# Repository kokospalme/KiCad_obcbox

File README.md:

# KiCad_obcbox
Hardware of the obcbox-project. This PCB is designed for a raspberry pi 3 B+ and an 0.96" OLED screen (be careful with the display-pinout!)
* Software (main): [java-BC](https://github.com/kokospalme/java-BC/tree/obcbox)
* Software (gui): [obcgui](https://github.com/kokospalme/obcgui/)
* Hardware (pcb): [KiCad_obcbox](https://github.com/kokospalme/KiCad_obcbox)
* Hardware (case): [grabcad](https://grabcad.com/library/obcbox-enclosure-v1-0-1)

# Status quo

* [v0.2 is working](https://github.com/kokospalme/KiCad_obcbox/releases)

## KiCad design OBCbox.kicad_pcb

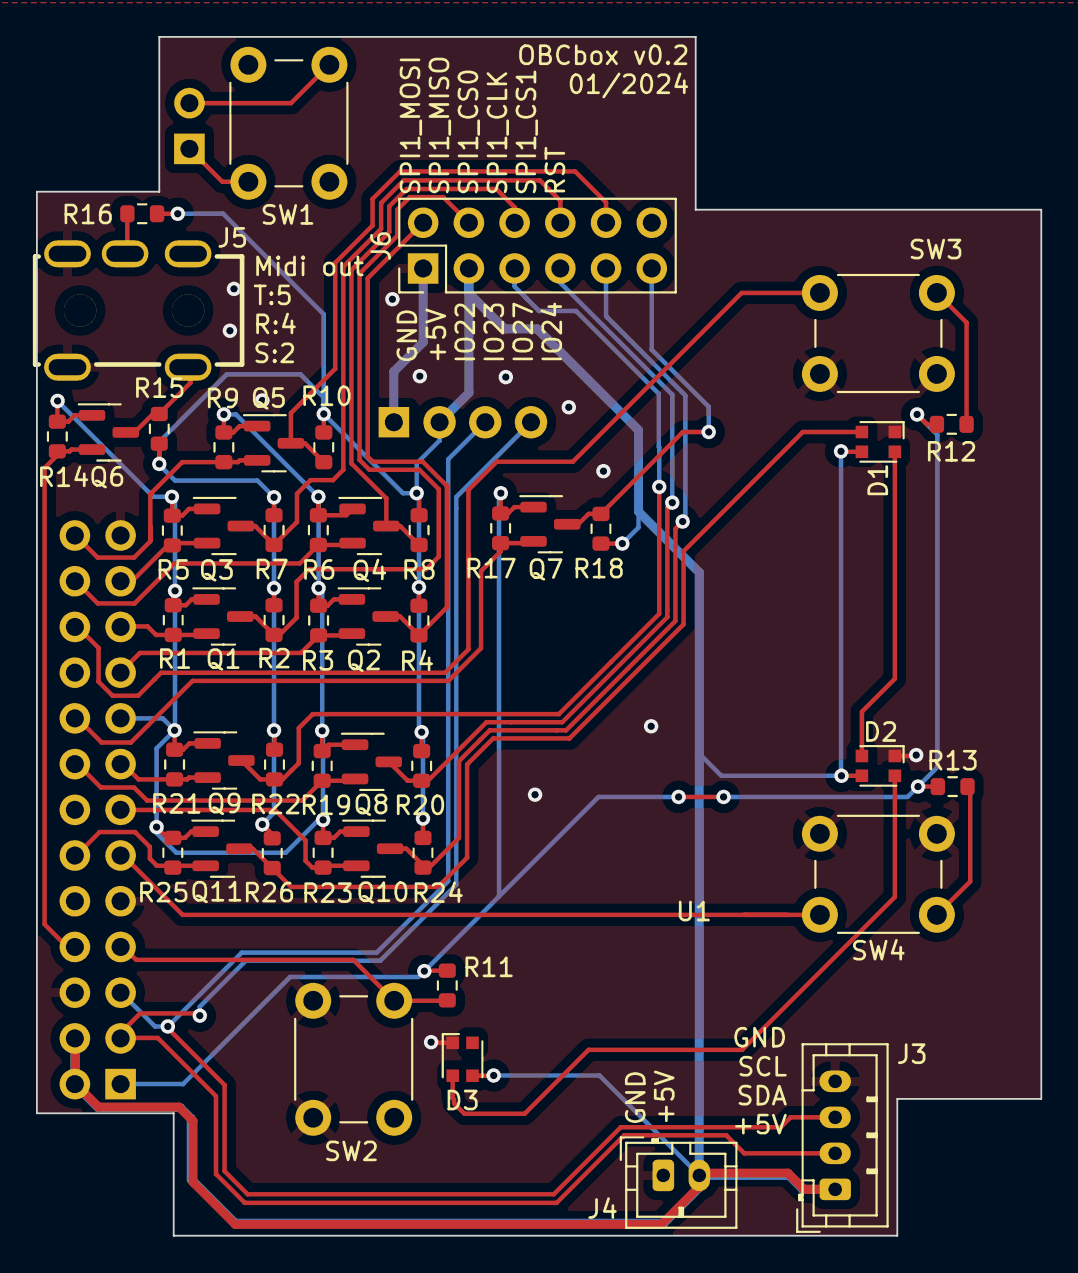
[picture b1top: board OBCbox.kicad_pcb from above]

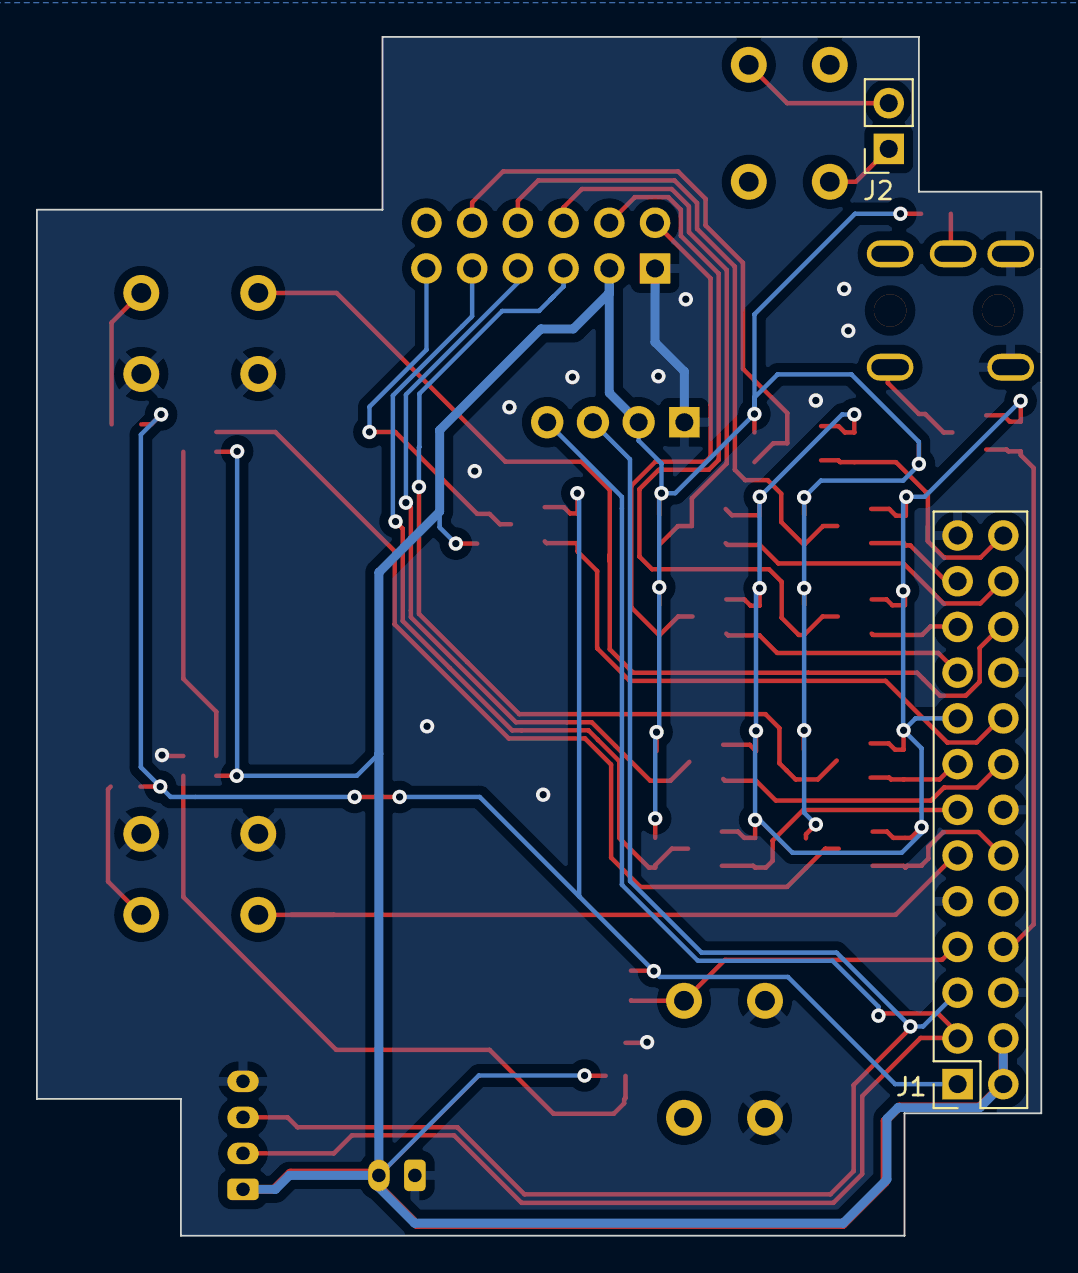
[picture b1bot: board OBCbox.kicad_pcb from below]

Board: 2 copper layers, 55.8 x 66.6 mm, 51 parts (2 on the bottom side), 35 nets.

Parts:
D1, D2, D3: WS2812C; LED_WS2812C-2020
J1: RASPI; PinSocket_2x13_P2.54mm_Vertical
J2: PI_RST; PinSocket_1x02_P2.54mm_Vertical
J3: I2C; JST_PH_B4B-PH-K_1x04_P2.00mm_Vertical
J4: PWR; JST_PH_B2B-PH-K_1x02_P2.00mm_Vertical
J5: WS28A; C18167_BOOMELE_Audiojack_withoutTip
J6: GPIO; PinHeader_2x06_P2.54mm_Vertical
Q1, Q2, Q3, Q4, Q5, Q6, Q7, Q8, Q9, Q10, Q11: BSS138; SOT-23
R1, R2, R3, R4, R5, R6, R7, R8, R9, R10, R11, R12, R13, R14, R17, R18, R19, R20, R21, R22, R23, R24, R25, R26: 10k; R_0603_1608Metric
R15, R16: 220Ω; R_0603_1608Metric
SW1: RST; SW_PUSH_6mm_H4.3mm
SW2: MA; SW_PUSH_6mm_H4.3mm
SW3: LAT_UP; SW_PUSH_6mm_H4.3mm
SW4: LAT_DOWN; SW_PUSH_6mm_H4.3mm
U1: OLED_0.96-I2C; SSD1306_OLED-0.96-128x64_I2C

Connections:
+3.3V: J1.1, J1.17, Q1.1 (G), Q2.1 (G), Q3.1 (G), Q4.1 (G), Q5.1 (G), Q6.1 (G), Q7.1 (G), Q8.1 (G), Q9.1 (G), Q10.1 (G), Q11.1 (G), R1.1, R3.1, R5.1, R6.1, R9.1, R11.1, R12.1, R13.1, R14.1, R17.1, R19.1, R21.1, R23.1, R25.1
+5V: D1.4 (VDD), D2.4 (VDD), D3.4 (VDD), J1.2, J1.4, J3.1, J4.2, J6.3, R2.1, R4.1, R7.1, R8.1, R10.1, R15.1, R16.1, R18.1, R20.1, R22.1, R24.1, R26.1, U1.2 (VCC)
/IO4: J1.7, R11.2, SW2.1
/IO17: J1.11, R13.2, SW4.1
/IO18: J1.12, Q11.2 (S), R25.2
/IO22: J1.15, Q9.2 (S), R21.2
/IO22_5V: J6.5, Q9.3 (D), R22.2
/IO23: J1.16, Q8.2 (S), R19.2
/IO23_5V: J6.7, Q8.3 (D), R20.2
/IO24: J1.18, Q7.2 (S), R17.2
/IO24_5V: J6.11, Q7.3 (D), R18.2
/IO25: J1.22, R12.2, SW3.1
/IO27: J1.13, Q10.2 (S), R23.2
/IO27_5V: J6.9, Q10.3 (D), R24.2
/MIDI_SNK_5: J5.T, Q6.3 (D), R15.2
/MIDI_SRC_4: J5.R, R16.2
/RST: J2.1, J6.12, SW1.2
/SCL: J1.5, J3.3, U1.3 (SCL)
/SDA: J1.3, J3.2, U1.4 (SDA)
/SPI_CLK: J1.23, Q3.2 (S), R5.2
/SPI_CS0: J1.24, Q4.2 (S), R6.2
/SPI_CS1: J1.26, Q5.2 (S), R9.2
/SPI_MISO: J1.21, Q1.2 (S), R1.2
/SPI_MOSI: J1.19, Q2.2 (S), R3.2
/UART_TX: J1.8, Q6.2 (S), R14.2
GND: D1.2 (GND), D2.2 (GND), D3.2 (GND), J1.6, J1.9, J1.14, J1.20, J1.25, J3.4, J4.1, J5.S, J6.1, SW2.2, SW3.2, SW4.2, U1.1 (GND)
unnamed: D1.3 (DI), Q11.3 (D), R26.2
unnamed: D1.1 (DO), D2.3 (DI)
unnamed: D2.1 (DO), D3.3 (DI)
unnamed: J2.2, SW1.1
SPI_CLK_5V: J6.8, Q3.3 (D), R7.2
SPI_CS0_5V: J6.6, Q4.3 (D), R8.2
SPI_CS1_5V: J6.10, Q5.3 (D), R10.2
SPI_MISO_5V: J6.4, Q1.3 (D), R2.2
SPI_MOSI_5V: J6.2, Q2.3 (D), R4.2

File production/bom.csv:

Designator,Footprint,Quantity,Value,LCSC Part #
"D1, D2, D3",LED_WS2812C-2020,3,WS2812C,C965556
J1,PinSocket_2x13_P2.54mm_Vertical,1,RASPI,
J2,PinSocket_1x02_P2.54mm_Vertical,1,PI_RST,
J3,JST_PH_B4B-PH-K_1x04_P2.00mm_Vertical,1,I2C,
J4,JST_PH_B2B-PH-K_1x02_P2.00mm_Vertical,1,PWR,
J5,C18167_BOOMELE_Audiojack_withoutTip,1,WS28A,
J6,PinHeader_2x06_P2.54mm_Vertical,1,GPIO,
"Q1, Q10, Q11, Q2, Q3, Q4, Q5, Q6, Q7, Q8, Q9",SOT-23,11,BSS138,
"R1, R10, R11, R12, R13, R14, R15, R16, R17, R18, R19, R2, R20, R21, R22, R23, R24, R25, R26, R3, R4, R5, R6, R7, R8, R9",0603,26,10k,
SW1,SW_PUSH_6mm_H4.3mm,1,RST,
SW2,SW_PUSH_6mm_H4.3mm,1,MA,
SW3,SW_PUSH_6mm_H4.3mm,1,LAT_UP,
SW4,SW_PUSH_6mm_H4.3mm,1,LAT_DOWN,
U1,SSD1306_OLED-0.96-128x64_I2C,1,OLED_0.96-I2C,

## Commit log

2024-02-12 v0.2 bugfixes
2024-02-12 update doc
